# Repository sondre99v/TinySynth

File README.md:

# TinySynth
A business card with a digital synthesizer, built with the [ATtiny817](https://www.microchip.com/wwwproducts/en/ATTINY817) microcontroller.

## Features
The business card features my name, contact information, and a digital synthesizer with integrated speakers and keyboard. To use the synthesizer, insert a suitable 3V coin cell battery (CR2016 or CR2032 works), and break off the stylus on the right side of the card. The stylus can then be used to play the keyboard, or to configure the synthesizer with the buttons above the keys.

### Configuration
The synthesizer can be configured using the buttons above the keys. The buttons, from 1 to 8 have the following functions:
  * Oscillator 1 octave: Cycle the octave of oscillator 1 between three settings
  * Oscillator 1 wavefrom: Cycle the waveform of oscillator 1 between sine, square, triangle, and sawtooth
  * Envelope rise time: Toggle slow attack on the envelope
  * Envelope fall time: Toggle slow release on the envelope
  * Oscillator 2 octave / disable: Cycle the octave of oscillator 2 between three settings, or disable oscillator 2
  * Oscillator 2 waveform: Cycle the waveform of oscillator 2 between sine, square, triangle, and sawtooth
  * Oscillator 2 detuning: Cycle the interval of oscillator 2 (above oscillator 1) between unison, third, fifth, and seventh
  * Oscillator 2 synchronize: Enable oscillator 2 reset on each completed period of oscillator 1
    
## Hardware
### Keyboard
The keyboard is designed to be read by the microcontroller with an ADC input. The current keyboard is the third revision of the circuit. 

The first design used a simple voltage divider with an 100 ohm resistor between each key, to generate a unique voltage on each key. The stylus was connected to the ADC input, and was used to sample the voltages. This did not work very well, as a very weak pull-resistor was needed on the stylus, but it was weak enough that just touching it caused disturbance to the voltage.

The second design was more similar to the traditional method used for analog synthesizers. The keys was again connected with 100 ohm resistors, but this time a simple current-mirror circuit was used to drive a constant current through the chain. The stylus was grounded, and when touched to a key it provided a shorter circuit to ground lowering the voltage needed to drive this current. This current was then measured by the ADC. This worked, but was sensitive to changes in supply voltage, and did not give very reliable measurements.

The third and current revision is similar to the second design, but it replaces the constant current driver with a simple resistor. The keyboard forms a simple voltage divider with a fixed top resistor of 10K ohm, and the resistor chain between the keys makes up the bottom resistor. As the sampled voltage is non-linearly related to the bottom resistor, the resistor values betwwen the keys were adjusted to compensate. Some non-linearity was allowed (and is corrected for in the software) to allow use of standard resistor values, and reduce the number of unique BOM items.

### Speakers
The speakers are very thin speakers which I believe is intended to be used in earbuds. They are connected in series, and driven using a speaker-driver amplifying the filtered output signal from the DAC in the microcontroller.

### Battery
The battery holder was designed into the PCB to allow the business card to remain as thin as possible. Some testing was done in advance (by dremeling a 1.6mm PCB to test-fit a battery) but mostly the design was copied from various online inspirations. This design worked really well on the first prototype PCB, so no modification was required, other than to add an indication of the correct polarity of the battery.

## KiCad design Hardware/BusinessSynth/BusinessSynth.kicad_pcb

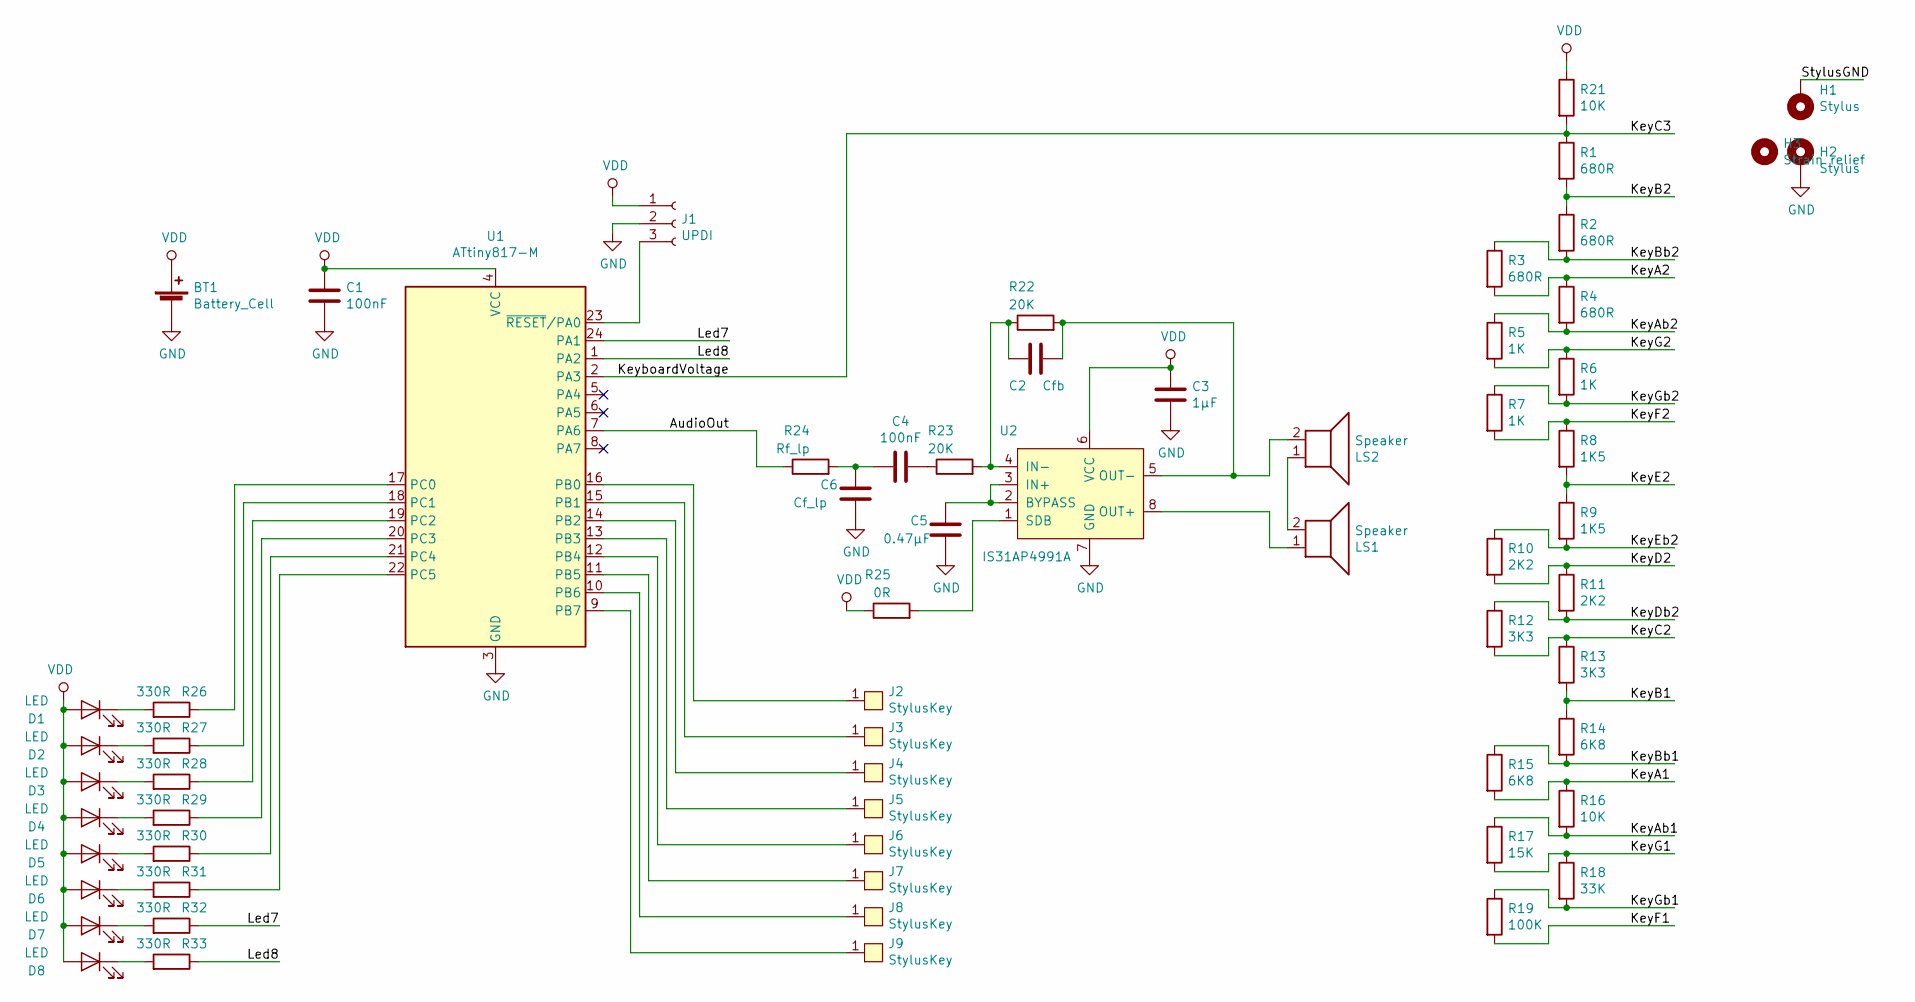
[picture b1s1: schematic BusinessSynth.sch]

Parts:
BT1: Battery_Cell; BatteryHolderPCB_CR20xx
C1, C4: 100nF; C_0402_1005Metric
C2: Cfb; C_0402_1005Metric
C3: 1µF; C_0402_1005Metric
C5: 0.47µF; C_0402_1005Metric
C6: Cf_lp; C_0402_1005Metric
D1, D2, D3, D4, D5, D6, D7, D8: LED; LED_0603_1608Metric_nosilk
H1, H2: Stylus; SolderWirePad_1x01_Drill0.8mm
H3: Strain relief; MountingHole_2.1mm
J1: UPDI; PinHeader_1x03_P2.54mm_Vertical
J2, J3, J4, J5, J6, J7, J8, J9: StylusKey
LS1, LS2: Speaker; CDMG13008L-02
R1, R2, R3, R4: 680R; R_0603_1608Metric_nosilk
R5, R6, R7: 1K; R_0603_1608Metric_nosilk
R8, R9: 1K5; R_0603_1608Metric_nosilk
R10, R11: 2K2; R_0603_1608Metric_nosilk
R12, R13: 3K3; R_0603_1608Metric_nosilk
R14, R15: 6K8; R_0603_1608Metric_nosilk
R16: 10K; R_0603_1608Metric_nosilk
R17: 15K; R_0603_1608Metric_nosilk
R18: 33K; R_0603_1608Metric_nosilk
R19: 100K; R_0603_1608Metric_nosilk
R21: 10K; R_0402_1005Metric
R22, R23: 20K; R_0402_1005Metric
R24: Rf_lp; R_0402_1005Metric
R25: 0R; R_0402_1005Metric
R26, R27, R28, R29, R30, R31, R32, R33: 330R; R_0402_1005Metric
U1: ATtiny817-M; QFN-24-1EP_4x4mm_P0.5mm_EP2.6x2.6mm_nosilk
U2: IS31AP4991A; MSOP-8-1EP_3x3mm_P0.65mm_nosilk

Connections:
/AudioOut: R24.1, U1.7 (PA6)
/KeyA1: R15.2, R16.1
/KeyA2: R3.2, R4.1
/KeyAb1: R16.2, R17.1
/KeyAb2: R4.2, R5.1
/KeyB1: R13.2, R14.1
/KeyB2: R1.2, R2.1
/KeyBb1: R14.2, R15.1
/KeyBb2: R2.2, R3.1
/KeyC2: R12.2, R13.1
/KeyC3: R1.1, R21.2, U1.2 (PA3)
/KeyD2: R10.2, R11.1
/KeyDb2: R11.2, R12.1
/KeyE2: R8.2, R9.1
/KeyEb2: R9.2, R10.1
/KeyF1: R19.2
/KeyF2: R7.2, R8.1
/KeyG1: R17.2, R18.1
/KeyG2: R5.2, R6.1
/KeyGb1: R18.2, R19.1
/KeyGb2: R6.2, R7.1
/Led7: R32.1, U1.24 (PA1)
/Led8: R33.1, U1.1 (PA2)
/StylusGND: H1.1
GND: BT1.2 (-), C1.2, C3.2, C5.2, C6.2, H2.1, J1.2, U1.3 (GND), U1.25 (GND), U2.7 (GND)
unnamed: C2.1, LS2.2, R22.2, U2.5 (OUT-)
unnamed: C2.2, R22.1, R23.2, U2.4 (IN-)
unnamed: C4.1, R23.1
unnamed: C4.2, C6.1, R24.2
unnamed: C5.1, U2.2 (BYPASS), U2.3 (IN+)
unnamed: D1.1 (K), R26.2
unnamed: D2.1 (K), R27.2
unnamed: D3.1 (K), R28.2
unnamed: D4.1 (K), R29.2
unnamed: D5.1 (K), R30.2
unnamed: D6.1 (K), R31.2
unnamed: D7.1 (K), R32.2
unnamed: D8.1 (K), R33.2
unnamed: J1.3, U1.23 (~RESET~/PA0)
unnamed: J2.1, U1.16 (PB0)
unnamed: J3.1, U1.15 (PB1)
unnamed: J4.1, U1.14 (PB2)
unnamed: J5.1, U1.13 (PB3)
unnamed: J6.1, U1.12 (PB4)
unnamed: J7.1, U1.11 (PB5)
unnamed: J8.1, U1.10 (PB6)
unnamed: J9.1, U1.9 (PB7)
unnamed: LS1.1, U2.8 (OUT+)
unnamed: LS1.2, LS2.1
unnamed: R25.2, U2.1 (SDB)
unnamed: R26.1, U1.17 (PC0)
unnamed: R27.1, U1.18 (PC1)
unnamed: R28.1, U1.19 (PC2)
unnamed: R29.1, U1.20 (PC3)
unnamed: R30.1, U1.21 (PC4)
unnamed: R31.1, U1.22 (PC5)
VDD: BT1.1 (+), C1.1, C3.1, D1.2 (A), D2.2 (A), D3.2 (A), D4.2 (A), D5.2 (A), D6.2 (A), D7.2 (A), D8.2 (A), J1.1, R21.1, R25.1, U1.4 (VCC), U2.6 (VCC)

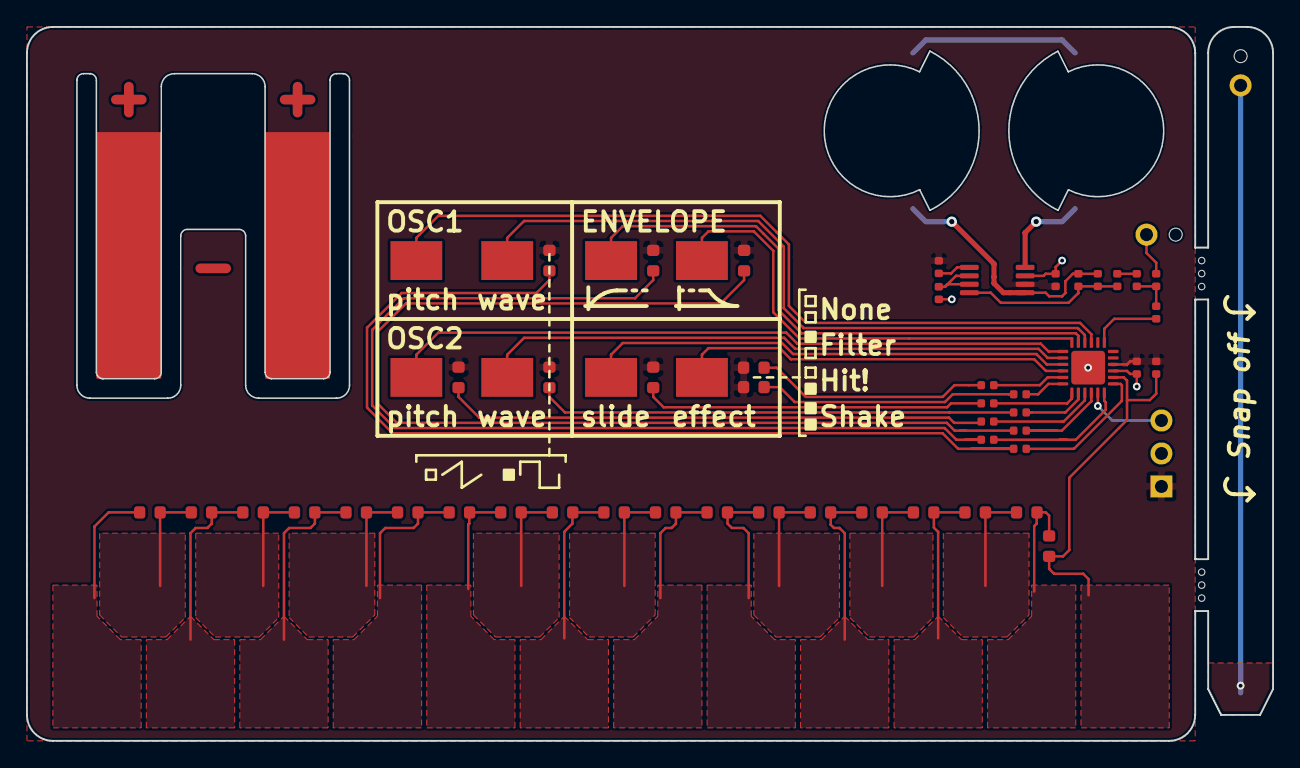
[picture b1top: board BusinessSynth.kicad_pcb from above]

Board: 2 copper layers, 96.0 x 55.0 mm, 64 parts (0 on the bottom side), 55 nets.

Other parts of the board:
H3#2: Strain relief; MountingHole_2.1mm

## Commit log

2019-02-19 Initial commit of project with basic synthesizer
2019-02-19 Start moving oscillators to their own module
2019-02-20 Fix some bugs causing no sound to be generated from oscillators
2019-02-22 Add .gitignore
2019-02-22 Fix move frequency changing out of ISR to fix timing issue
2019-02-22 Fix mixing and levels of oscillators
2019-02-22 Enable proper synchronous changing of frequency, and implement analog and digital inputs
2019-03-02 Implement basic keyboard reading
2019-03-04 Move to 16 bit waveform samples and amplitude. Bugged "envelope"
2019-03-04 Move oscillator handling to separate function. Moved away from delta-based DAC output
2019-03-05 Rotate phase of square and saw wave-data to align them with the sine and triangle
2019-03-05 Testing of amplitude modulation
2019-04-12 Added PCB project to repository
2019-04-12 Add project for business card synth
2019-04-12 Add Notes folder and excel sheet with resistor calculations
2019-04-12 Draw new keyboard circuit in the KiCAD schematic
2019-04-14 Add code for envelope and keyboard modules
2019-04-14 Update README.md
    Add descriptions of hardware and features.
2019-04-14 Add images to use in the readme
2019-04-14 Reduce size of, and crop images
2019-04-14 Add images to README.md
2019-04-24 Change resistor chain in schematic to simpler solution
2019-04-24 Add Excel sheet with resistor calculations
2019-04-24 Extend basic framework for synthesizer modules
2019-04-25 Change oscillators to use 8 bit values
2019-04-25 Connect keyboard and envelope modules
2019-04-25 Add config panel module
2019-04-26 Add images of voltage measurements
2019-04-26 Wire up the rest of the patch panel
2019-04-26 Improve configuration of synth
2019-06-24 Add noise waveform to oscillator
2019-06-24 Implement full, instantiatable, ADSR envelope generator
2019-06-24 Fix line endings and remove extra whitespace
2019-06-26 Add hold timer to envelope
2019-08-12 Add glide functionality to oscillator
2019-08-12 Remove sync. Add reset at zero amplitude. Add oscA enabled
2019-08-12 Implement new envelope interface, and test VCF
2019-08-23 Start layout of new patch-panel
2019-08-24 Fix speaker-driver footprint, and complete new routing
2019-08-25 Add new envelope implementation files
2019-08-26 Update keyboard module to more modular design
2019-08-26 WIP: Connect filter and EG correctly
2019-08-27 Fix modulation of filter
2019-08-27 Start writing modulated parameter util
2019-08-28 Hide contact information in README image
2019-08-28 Remove old envelope files
2019-08-28 Rename new envelope files
2019-09-04 Fix envelope so that it also decays after release
2019-09-23 Finalize PCB for rev 2
2019-09-23 Generate gerbers for PCB rev 2
2020-01-06 Remove led PWM and EG3 init values
2020-01-06 Fix patch panel for new PCB
2020-01-06 Precompute TC target values
2020-01-06 Move slide to keyboard
2020-01-07 Remove oscillator detune feature
2020-01-07 Fix wave selection buttons for new PCB
2020-01-07 Fix pitch buttons for new PCB
2020-01-07 Add basic implementation of filter effect
2020-01-07 Simplify envelope generators
2020-01-07 Improve implementation of filter effect
2020-01-07 Add LFO module, and implement temporary example
2020-01-08 Add hit effect and fix simultaneous slide and shake
2020-01-08 Fix warnings and whitespace
2020-01-10 All features working
2020-01-10 Fix sliding not continuing when key is released
